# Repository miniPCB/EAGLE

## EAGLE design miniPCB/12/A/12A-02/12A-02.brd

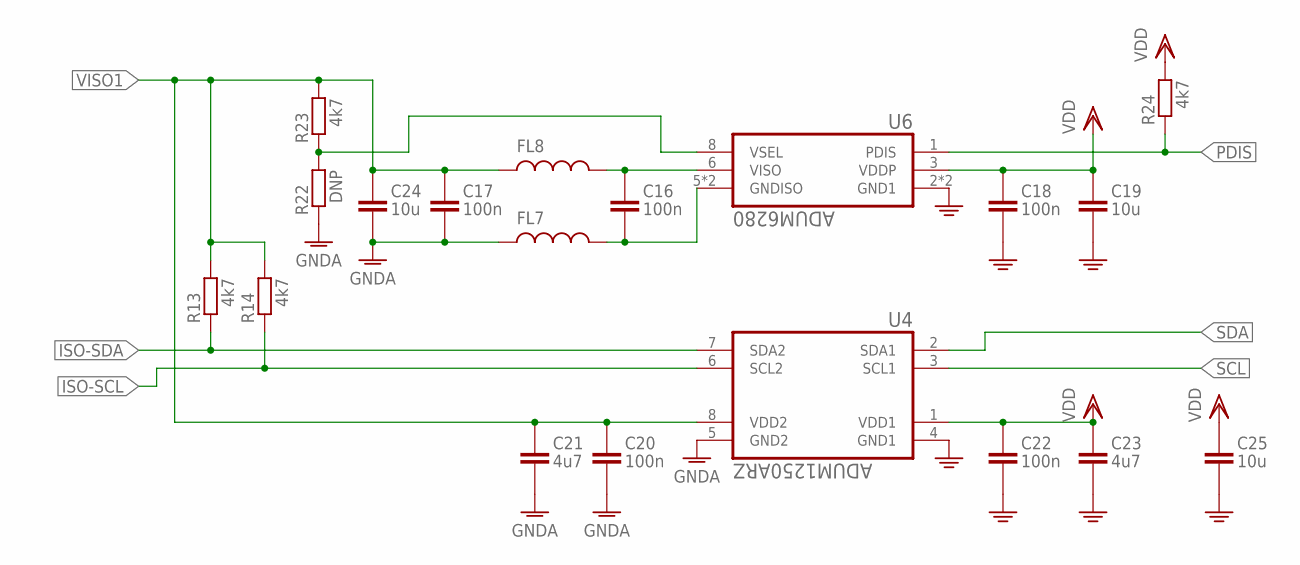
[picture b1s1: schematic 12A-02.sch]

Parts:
C16, C17, C18, C20, C22: 100n; C0402
C19, C24, C25: 10u; C0805
C21, C23: 4u7; C0402
FL7, FL8: BLM03HG601SZ1D; R0402
R13, R14, R23, R24: 4k7; R0402
R22: DNP; R0402
U4: ADUM1250ARZ; SOIC127P600X175-8N
U6: ADUM6280; SOIC127P600X175-8N

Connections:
GND: C18.2 (-), C19.2ASDF (-), C22.2 (-), C23.2 (-), C25.2ASDF (-), U4.4 (GND1), U6.2 (GND1), U6.4 (GND1)
GNDA: C17.2 (-), C20.2 (-), C21.2 (-), C24.2ASDF (-), FL7.1, R22.1, U4.5 (GND2)
ISO-SCL: R14.1, U4.6 (SCL2)
ISO-SDA: R13.1, U4.7 (SDA2)
unnamed: R22.2, R23.1, U6.8 (VSEL)
unnamed: C16.2 (-), FL7.2, U6.5 (GNDISO), U6.7 (GNDISO)
unnamed: C16.1 (+), FL8.2, U6.6 (VISO)
PDIS: R24.1, U6.1 (PDIS)
SCL: U4.3 (SCL1)
SDA: U4.2 (SDA1)
VDD: C18.1 (+), C19.1ASD (+), C22.1 (+), C23.1 (+), C25.1ASD (+), R24.2, U4.1 (VDD1), U6.3 (VDDP)
VISO1: C17.1 (+), C20.1 (+), C21.1 (+), C24.1ASD (+), FL8.1, R13.2, R14.2, R23.2, U4.8 (VDD2)

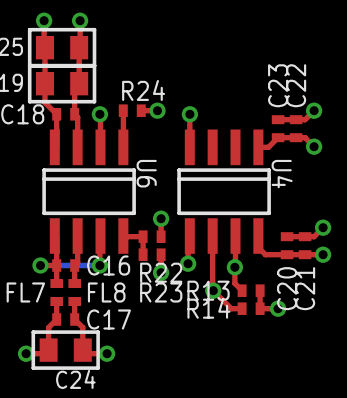
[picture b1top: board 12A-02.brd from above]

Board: 2 copper layers, 19 parts (0 on the bottom side), 10 nets.

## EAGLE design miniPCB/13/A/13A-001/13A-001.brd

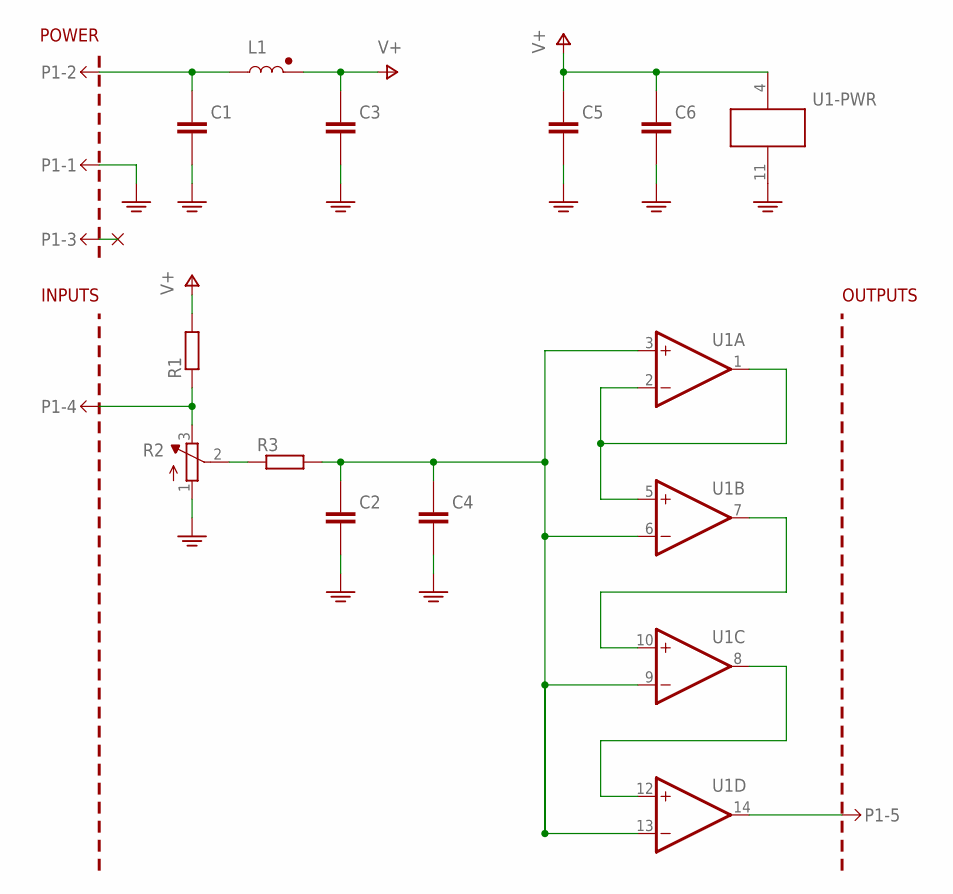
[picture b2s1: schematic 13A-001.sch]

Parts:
C1, C3: CAPACITOR_10; C5MM
C2, C4, C5, C6: CAPACITORTHD; C050-024X044
L1: INDUCTORRFS1113; L/RFS1113
P1-: MINIPCB_5P50X50; MINIPCB_5P_50X50MM
R1, R3: RESISTORTHD; 0204/10
R2: TRIMPOT0.100THD; TRIM_0100
U1: OPAMP_QUADTHD; DIL14

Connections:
GND: C1.-, C2.2 (-), C3.-, C4.2 (-), C5.2 (-), C6.2 (-), P1-.1, R2.1 (A), U1.11 (V-)
unnamed: P1-.4, R1.1, R2.3 (E)
unnamed: R2.2 (S), R3.1
unnamed: C2.1 (+), C4.1 (+), R3.2, U1.3 (+IN), U1.6 (-IN), U1.9 (-IN), U1.13 (-IN)
unnamed: U1.1 (OUT), U1.2 (-IN), U1.5 (+IN)
unnamed: C1.+, L1.2, P1-.2
unnamed: U1.7 (OUT), U1.10 (+IN)
unnamed: U1.8 (OUT), U1.12 (+IN)
unnamed: P1-.5, U1.14 (OUT)
V+: C3.+, C5.1 (+), C6.1 (+), L1.1, R1.2, U1.4 (V+)

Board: 2 copper layers, 12 parts (0 on the bottom side), 10 nets, no tracks yet.

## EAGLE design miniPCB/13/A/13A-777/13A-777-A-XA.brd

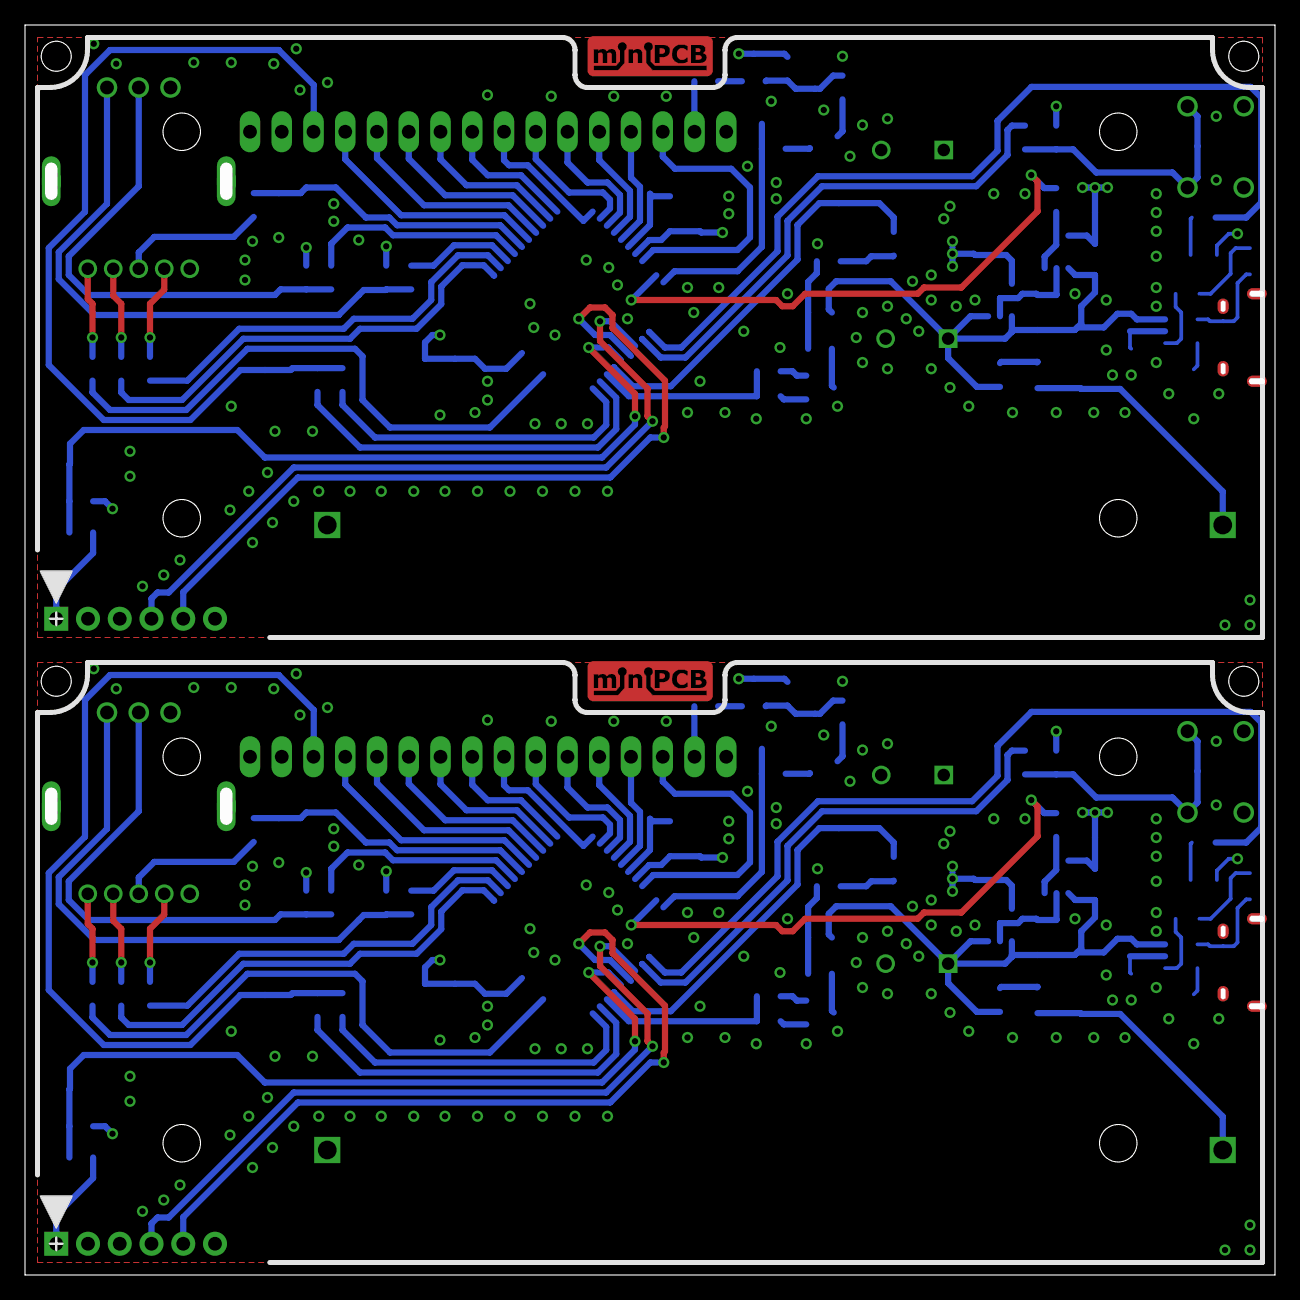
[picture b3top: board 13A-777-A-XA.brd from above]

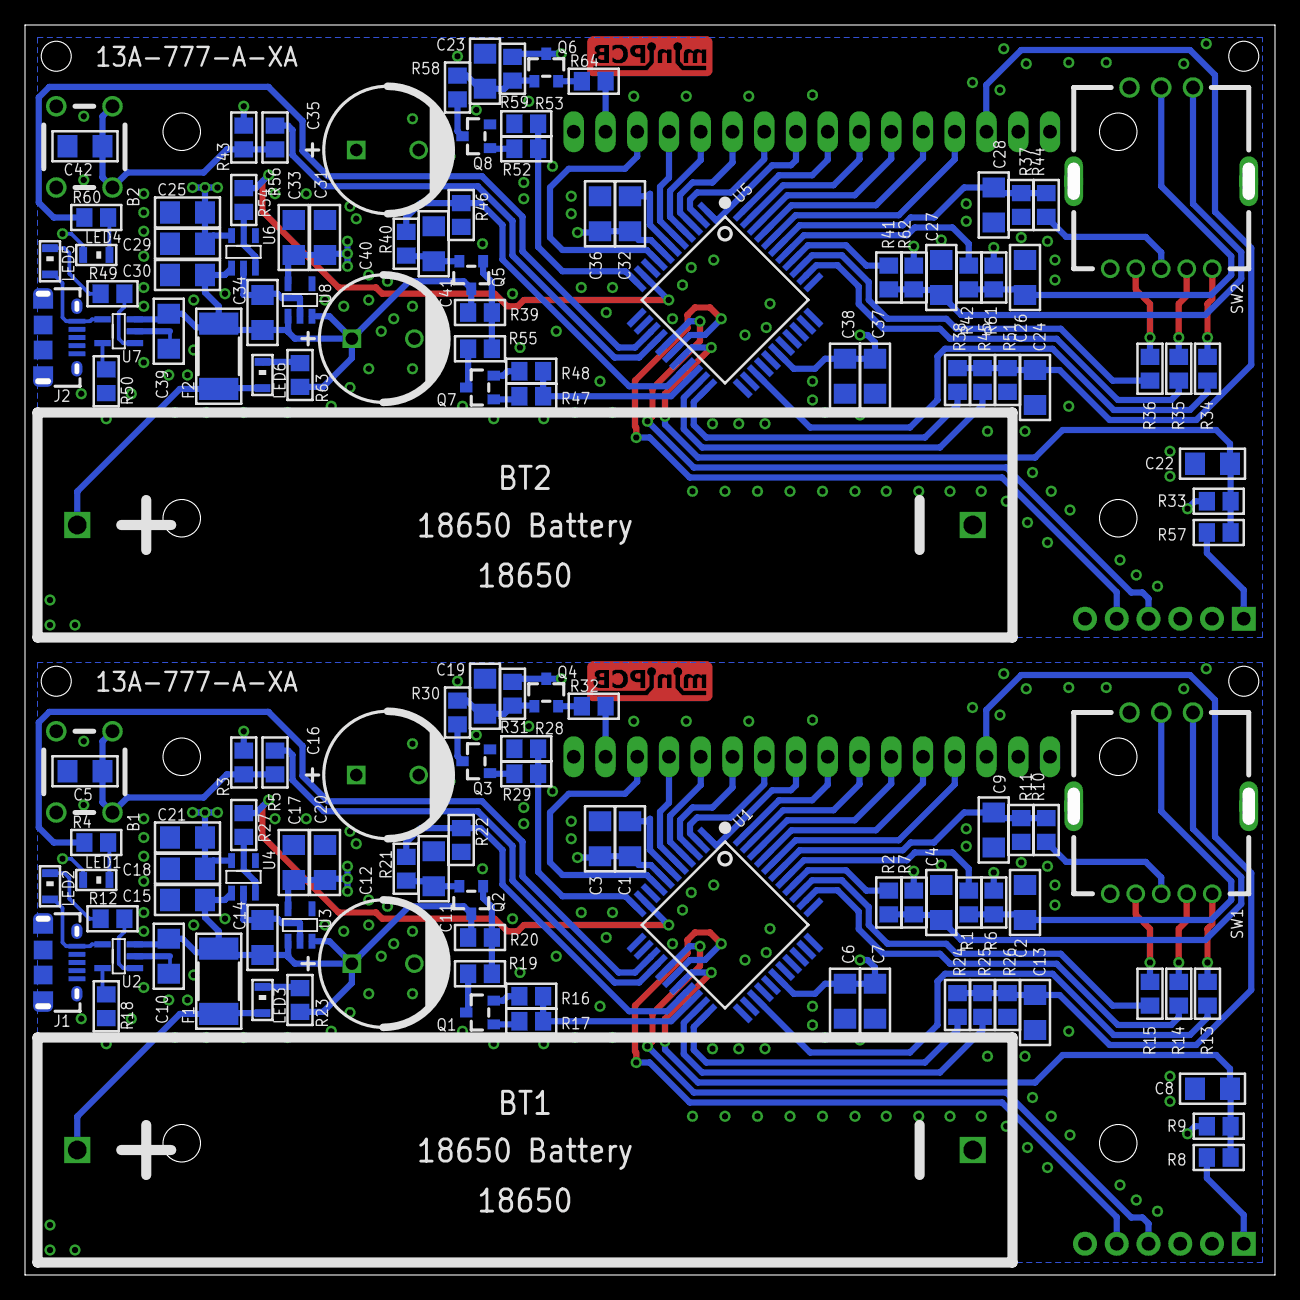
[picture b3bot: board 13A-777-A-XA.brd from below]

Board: 4 copper layers, 100.0 x 100.0 mm, 145 parts (138 on the bottom side), 116 nets.

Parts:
B1, B2: 6X6MM
BT1, BT2: 18650; BATTERY-18650-1-NOHOLES
C1, C2, C4, C5, C6, C8, C9, C11, C13, C14, C15, C19, C20, C21, C22, C23, C24, C25, C26, C27, C28, C30, C31, C32, C34, C38, C41, C42: 680n; C1206
C3, C7, C17, C18, C29, C33, C36, C37: 6n8; C1206
C10, C39: 4u7; C1206
C12, C16, C35, C40: 22u 25V; C5MM
E$1: MINIPCB_PANEL_IMAGEFRAME
F1, F2: 1A; 1812L010DR
J1, J2: USB_MICRO
LED1, LED2, LED3, LED4, LED5, LED6: CHIP-LED0805
PCB, PCB1: PCB-50/100-0; MINIPCB_0P_50X100MM
Q1, Q3, Q7, Q8: 2N7002; SOT23
Q2, Q4, Q5, Q6: NTR2101P; SOT23
R1, R2, R6, R7, R9, R16, R17, R19, R28, R29, R30, R33, R41, R42, R47, R48, R52, R53, R55, R58, R61, R62: 10k; R0805
R3, R5, R10, R43, R44, R56: 10K; R0805
R4, R8, R12, R13, R14, R15, R23, R27, R32, R34, R35, R36, R49, R54, R57, R60, R63, R64: 150; R0805
R11, R20, R31, R37, R39, R59: 499K; R0805
R18, R50: 2K; R0805
R21, R22, R40, R46: 4K99; R0805
R24, R25, R26, R38, R45, R51: 1K; R0805
SW1, SW2: PEL12T; SWITCH-ROTARY_ENCODER-12MM
U1, U5: PIC16F1789T-I/PT; SQFP-S-10X10-44
U2, U7: MCP73831; SOT-23-5_MC_MCH
U3, U4, U6, U8: ADP150AUJZ-3.3-R7; SOT25
U$1, U$2: PICKIT3ARROW; PINS_6_PICKIT3
X1, X2: HD44780LCD-1602; LCD1602

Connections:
+3V1: C31.+, C32.+, C33.+, C36.+, C37.+, C38.+, LED4.A, R33.2, R43.2, U5.7, U5.28, U8.5, U$2.2
+3V3: C1.+, C3.+, C6.+, C7.+, C17.+, C20.+, LED1.A, R3.2, R9.2, U1.7, U1.28, U3.5, U$1.2
+3V3-LCD: C16.+, C18.+, C21.+, Q4.3, R6.2, R7.2, R31.1, SW1.5, U4.5, X1.2
+3V3-LCD1: C25.+, C29.+, C35.+, Q6.3, R59.1, R61.2, R62.2, SW2.5, U6.5, X2.2
B1: B1.3.B, B1.4.B, C5.+, R3.1, R5.2
B2: B2.3.B, B2.4.B, C42.+, R43.1, R56.2
BT+: BT1.+, F1.1, LED3.A
BT+1: BT2.+, F2.1, LED6.A
BUTTON: R5.1, U1.15
BUTTON1: R56.1, U5.15
ENC_A: R1.2, U1.38
ENC_A1: R42.2, U5.38
ENC_B: R2.2, U1.37
ENC_B1: R41.2, U5.37
ENC_BLUE: R15.1, U1.36
ENC_BLUE1: R36.1, U5.36
ENC_GREEN: R14.1, U1.35
ENC_GREEN1: R35.1, U5.35
ENC_RED: R13.1, U1.25
ENC_RED1: R34.1, U5.25
ENC_SW: C9.+, R10.1, R11.2, U1.39
ENC_SW1: C28.+, R37.2, R44.1, U5.39
GND: B1.1.A, B1.2.A, BT1.1, C1.-, C2.-, C3.-, C4.-, C5.-, C6.-, C7.-, C8.-, C9.-, C10.-, C11.-, C12.-, C13.-, C14.-, C15.-, C16.-, C17.-, C18.-, C19.-, C20.-, C21.-, J1.5, Q1.2, Q3.2, R11.1, R16.2, R18.2, R22.1, R26.2, R28.2, SW1.C, U1.6, U1.29, U2.2, U3.2, U4.2, U$1.3, X1.1, X1.16
GND1: B2.1.A, B2.2.A, BT2.1, C22.-, C23.-, C24.-, C25.-, C26.-, C27.-, C28.-, C29.-, C30.-, C31.-, C32.-, C33.-, C34.-, C35.-, C36.-, C37.-, C38.-, C39.-, C40.-, C41.-, C42.-, J2.5, Q7.2, Q8.2, R37.1, R46.1, R48.2, R50.2, R51.2, R53.2, SW2.C, U5.6, U5.29, U6.2, U7.2, U8.2, U$2.3, X2.1, X2.16
ICSPCLK: U1.17, U$1.5
ICSPCLK1: U5.17, U$2.5
ICSPDAT: U1.16, U$1.4
ICSPDAT1: U5.16, U$2.4
LCD-BACKLIGHT-A: R32.2, X1.15
LCD-BACKLIGHT-A1: R64.2, X2.15
LCD-BACKLIGHT-ENABLE: R28.1, R29.2, U1.11
LCD-BACKLIGHT-ENABLE1: R52.2, R53.1, U5.11
LCD-D0: U1.43, X1.7
LCD-D1: U1.44, X1.8
LCD-D2: U1.1, X1.9
LCD-D3: U1.2, X1.10
LCD-D4: U1.3, X1.11
LCD-D5: U1.4, X1.12
LCD-D6: U1.5, X1.13
LCD-D7: U1.8, X1.14
LCD-D8: U5.44, X2.8
LCD-D9: U5.1, X2.9
LCD-D10: U5.2, X2.10
LCD-D11: U5.43, X2.7
LCD-D12: U5.3, X2.11
LCD-D13: U5.4, X2.12
LCD-D14: U5.5, X2.13
LCD-D15: U5.8, X2.14
LCD-RE: U1.42, X1.6
LCD-RE1: U5.42, X2.6
LCD-RS: U1.40, X1.4
LCD-RS1: U5.40, X2.4
LCD-RW: U1.41, X1.5
LCD-RW1: U5.41, X2.5
LCD-V0: C13.+, R24.1, R25.1, R26.1, X1.3
LCD-V1: C24.+, R38.1, R45.1, R51.1, X2.3
LCD_ENABLE: R27.2, U1.10
LCD_ENABLE1: R54.2, U5.10
LED1: R4.1, U1.14
LED1.K: LED1.C, R4.2
LED1.K1: LED4.C, R60.2
LED2: R60.1, U5.14
LED2.K: LED2.C, R12.2
LED2.K1: LED5.C, R49.2
LED3K: LED3.C, R23.2
LED3K1: LED6.C, R63.2
MCLR: C8.+, R8.1, R9.1, U1.18
MCLR1: C22.+, R33.1, R57.1, U5.18
P1-1: R8.2, U$1.1
P1-2: R57.2, U$2.1
PROG: R18.1, U2.5
PROG1: R50.1, U7.5
Q1.D: Q1.3, R19.2
Q1.D1: Q7.3, R55.2
Q1.G: Q1.1, R17.1
Q1.G1: Q7.1, R47.1
Q2.G: Q2.1, R19.1, R20.2
Q2.G1: Q5.1, R39.2, R55.1
Q2.S: C11.+, Q2.2, R21.2
Q2.S1: C41.+, Q5.2, R40.2
Q3.D: Q3.3, R30.2
Q3.D1: Q8.3, R58.2
Q3.G: Q3.1, R29.1
Q3.G1: Q8.1, R52.1
Q4.G: C19.+, Q4.1, R30.1, R31.2
Q4.G1: C23.+, Q6.1, R58.1, R59.2
Q4.S: Q4.2, R32.1
Q4.S1: Q6.2, R64.1
RA0: R21.1, R22.2, U1.19
RA1: R16.1, R17.2, U1.20
RA2: R25.2, U1.21
RA3: R24.2, U1.22
RA4: R45.2, U5.21
RA5: R40.1, R46.2, U5.19
RA6: R38.2, U5.22
RA7: R47.2, R48.1, U5.20
SW1.1: R13.2, SW1.1
SW1.2: R14.2, SW1.2
SW1.3: R10.2, SW1.3
SW1.4: R15.2, SW1.4
SW1.5: R34.2, SW2.1
SW1.6: R35.2, SW2.2
SW1.7: R36.2, SW2.4
SW1.8: R44.2, SW2.3
SW1.A: C2.+, R1.1, R6.1, SW1.B
SW1.A1: C26.+, R42.1, R61.1, SW2.B
SW1.B: C4.+, R2.1, R7.1, SW1.A
SW1.B1: C27.+, R41.1, R62.1, SW2.A
U4.1: R12.1, U2.1
U4.2: R49.1, U7.1
U4.3: R27.1, U4.3
U4.4: R54.1, U6.3
VBAT: C10.+, C12.+, C14.+, C15.+, F1.2, Q2.3, R20.1, R23.1, U2.3, U3.1, U3.3, U4.1
VBAT1: C30.+, C34.+, C39.+, C40.+, F2.2, Q5.3, R39.1, R63.1, U6.1, U7.3, U8.1, U8.3
VUSB: J1.1, LED2.A, U2.4
VUSB1: J2.1, LED5.A, U7.4

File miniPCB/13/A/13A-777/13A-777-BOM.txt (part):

Partlist exported from C:/Repos/miniPCB/EAGLE/miniPCB/13/A/13A-777/13A-777.sch at 2/3/2023 6:44 PM

Qty Value             Device                               Package                    Parts                                                         Description                                                   ARROW_PART_NUMBER ARROW_PRICE-STOCK                                                    COPYRIGHT                                                DESCRIPTION                                                   HEIGHT MANUFACTURER_NAME MANUFACTURER_PART_NUMBER MFR_NAME  MOUSER_PART_NUMBER MOUSER_PRICE-STOCK                                                                              MOUSER_TESTING_PART_NUMBER MOUSER_TESTING_PRICE-STOCK PART_NUMBER  REVISION
3                     LEDCHIP-LED0805                      CHIP-LED0805               LED1, LED2, LED3                                              LED                                                                                                                                                                                                                                                                                                                                                                                                                                                                                                                                   
1                     PUSHBUTTON6X6MM                      6X6MM                      B1                                                            Tactile push button switch                                                                                                                                                                                                                                                                                                                                                                                                                                                                                                            
1                     USB                                  USB_MICRO                  J1                                                                                                                                                                                                                                                                                                                                                                                                                                                                                                                                                                                                  
3   10K               RESISTORSMD                          R0805                      R3, R5, R10                                                                                                                                                                                                                                                                                                                                                                                                                                                                                                                                                                                         
11  10k               RESISTORSMD                          R0805                      R1, R2, R6, R7, R9, R16, R17, R19, R28, R29, R30                                                                                                                                                                                                                                                                                                                                                                                                                                                                                                                                                    
9   150               RESISTORSMD                          R0805                      R4, R8, R12, R13, R14, R15, R23, R27, R32                                                                                                                                                                                                                                                                                                                                                                                                                                                                                                                                                           
1   18650             BATTERY18650-NOHOLES                 BATTERY-18650-1-NOHOLES    BT1                                                           2xAAA battery holder for VIVA                                                                                                                                                                                                                                                                                                                                                                                                                                                                                                         
1   1A                FUSE-1812-1A                         1812L010DR                 F1                                                            Resettable Fuses - PPTC PTC 60V POLYFUSE SURF MOUNT 1812 0.5A 1812L050/60MR     https://www.arrow.com/en/products/1812l05060mr/littelfuse?re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                                                          Resettable Fuses - PPTC PTC 60V POLYFUSE SURF MOUNT 1812 0.5A 1.25mm LITTELFUSE        1812L050/60MR                      576-1812L050/60MR  https://www.mouser.co.uk/ProductDetail/Littelfuse/1812L050-6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                                                                            
3   1K                RESISTORSMD                          R0805                      R24, R25, R26                                                                                                                                                                                                                                                                                                                                                                                                                                                                                                                                                                                       
2   22u 25V           CAPACITOR_10                         C5MM                       C12, C16                                                                                                                                                                                                                                                                                                                                                                                                                                                                                                                                                                                            
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
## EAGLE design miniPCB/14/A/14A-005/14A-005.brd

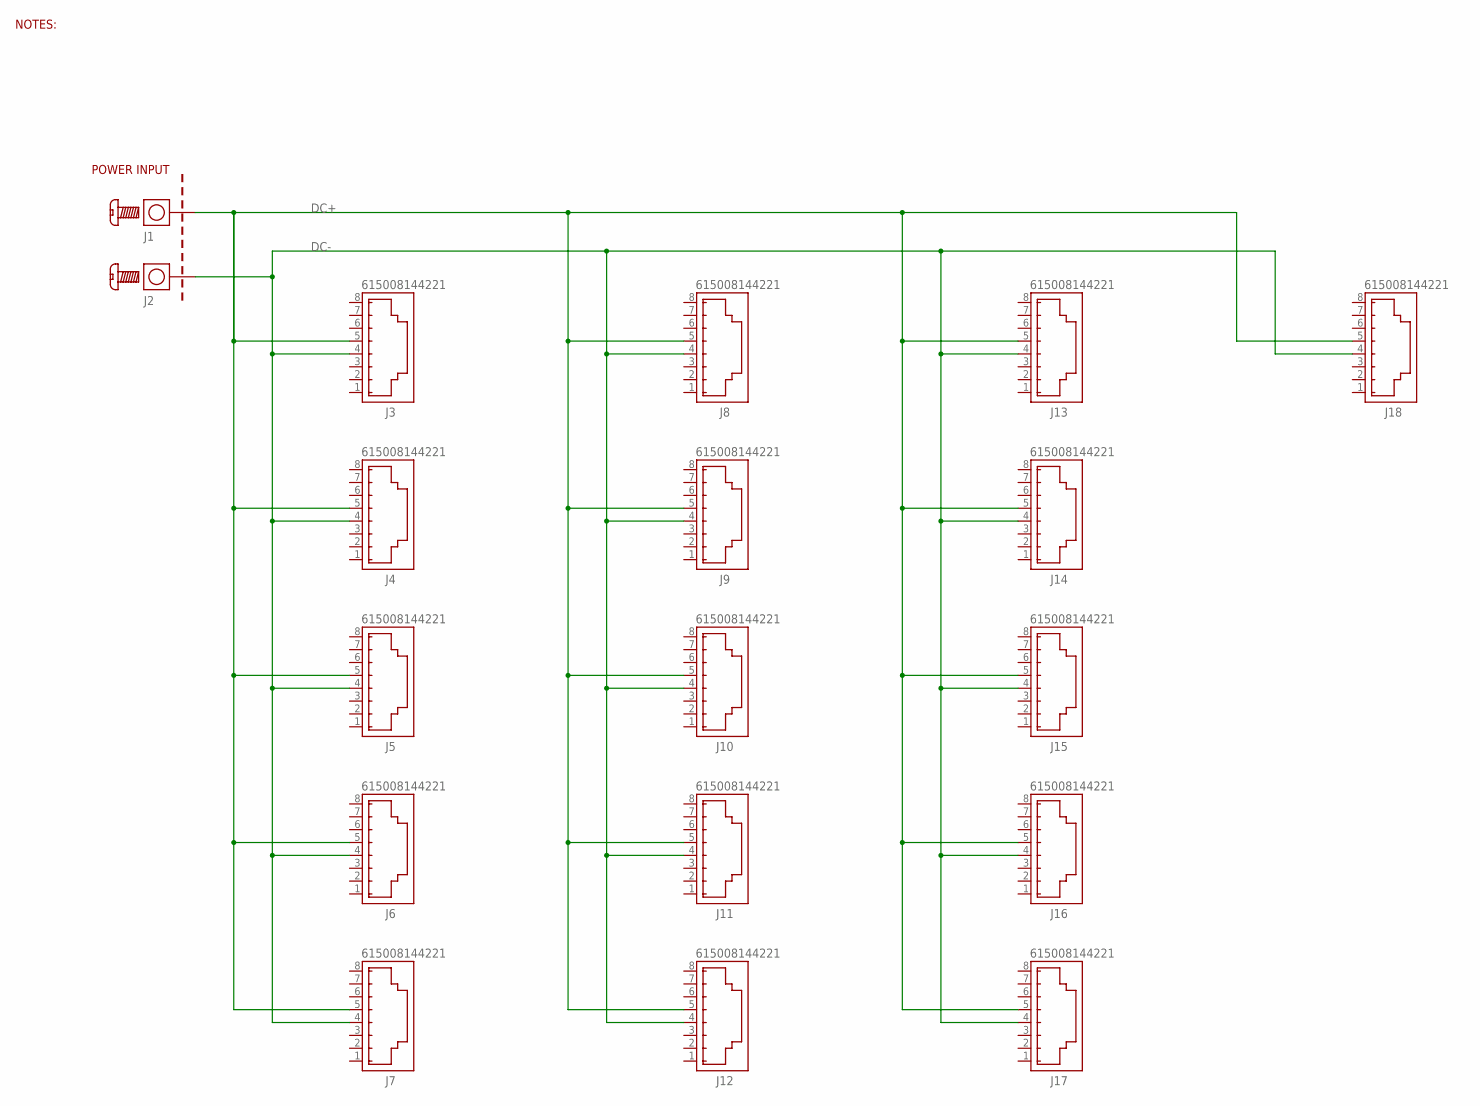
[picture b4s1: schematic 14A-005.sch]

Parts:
-: POWER INPUT; MINIPCB_DOCK_100X100; PART_NUMBER 14A-005
J1, J2: SCREW-TERMINAL; SCREW-TERMINAL-M3
J3, J4, J5, J6, J7, J8, J9, J10, J11, J12, J13, J14, J15, J16, J17, J18: 615008144221

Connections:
DC+: J1.1, J1.2, J1.3, J1.4, J3.5 (4), J4.5 (4), J5.5 (4), J6.5 (4), J7.5 (4), J8.5 (4), J9.5 (4), J10.5 (4), J11.5 (4), J12.5 (4), J13.5 (4), J14.5 (4), J15.5 (4), J16.5 (4), J17.5 (4), J18.5 (4)
DC-: J2.1, J2.2, J2.3, J2.4, J3.4 (5), J4.4 (5), J5.4 (5), J6.4 (5), J7.4 (5), J8.4 (5), J9.4 (5), J10.4 (5), J11.4 (5), J12.4 (5), J13.4 (5), J14.4 (5), J15.4 (5), J16.4 (5), J17.4 (5), J18.4 (5)

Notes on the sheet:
NOTES:

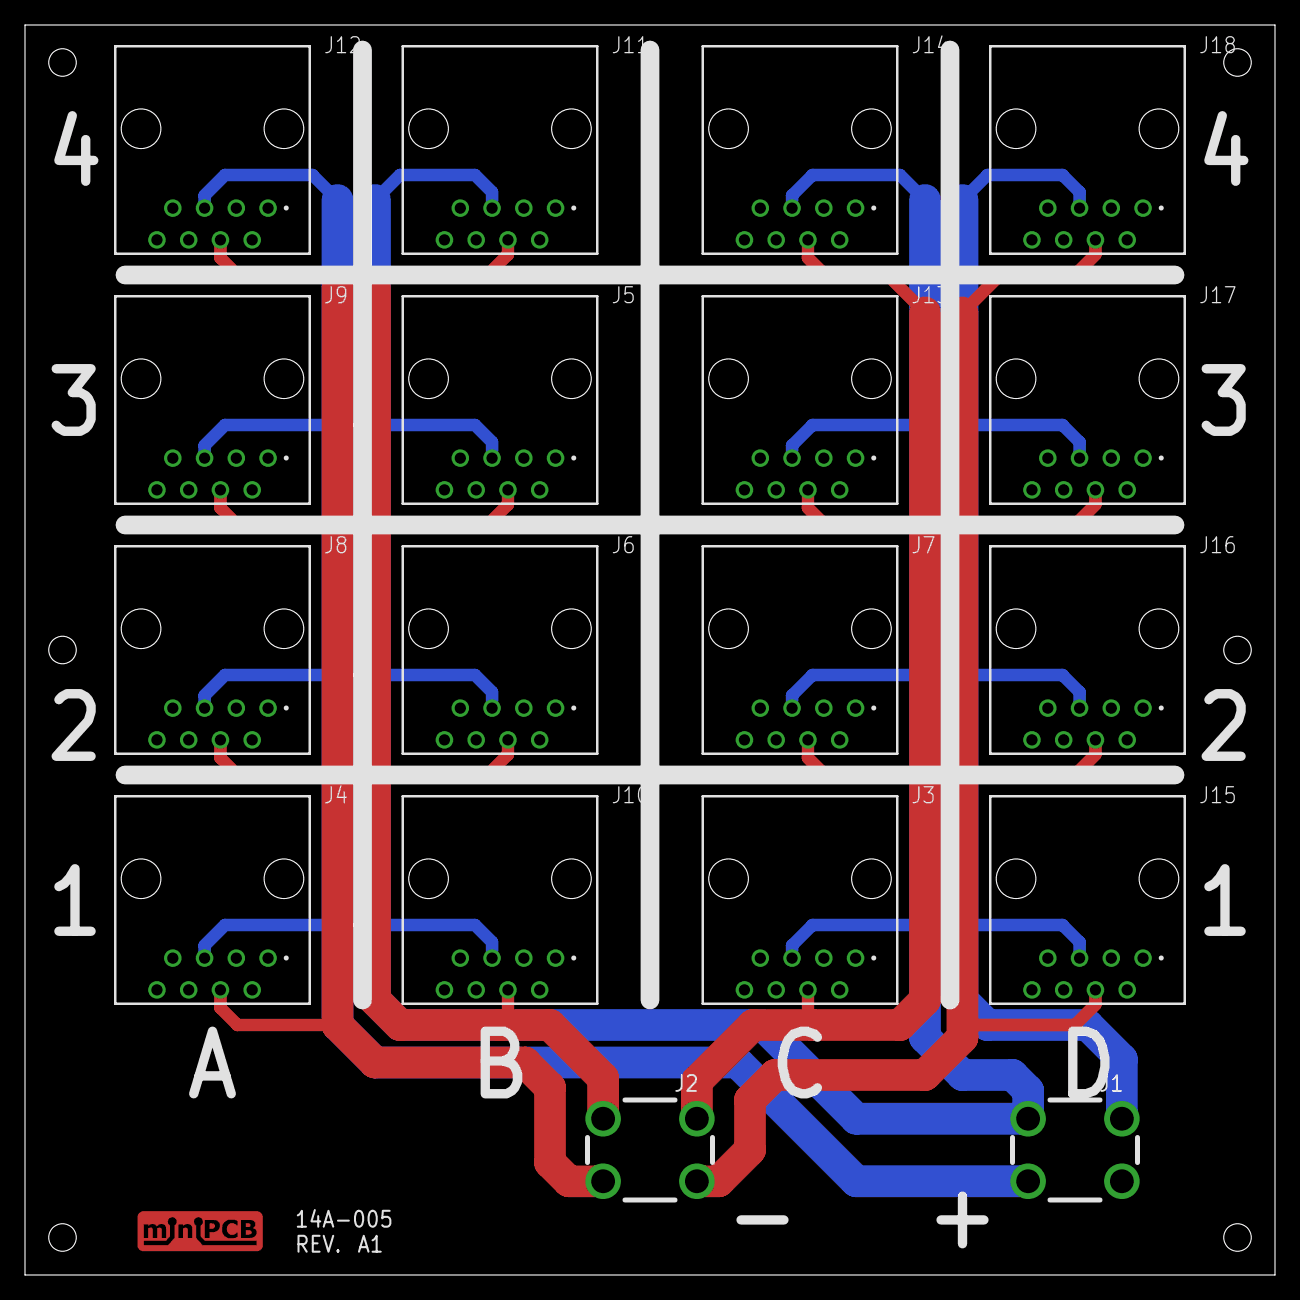
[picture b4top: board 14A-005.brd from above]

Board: 2 copper layers, 100.0 x 100.0 mm, 19 parts (0 on the bottom side), 2 nets.

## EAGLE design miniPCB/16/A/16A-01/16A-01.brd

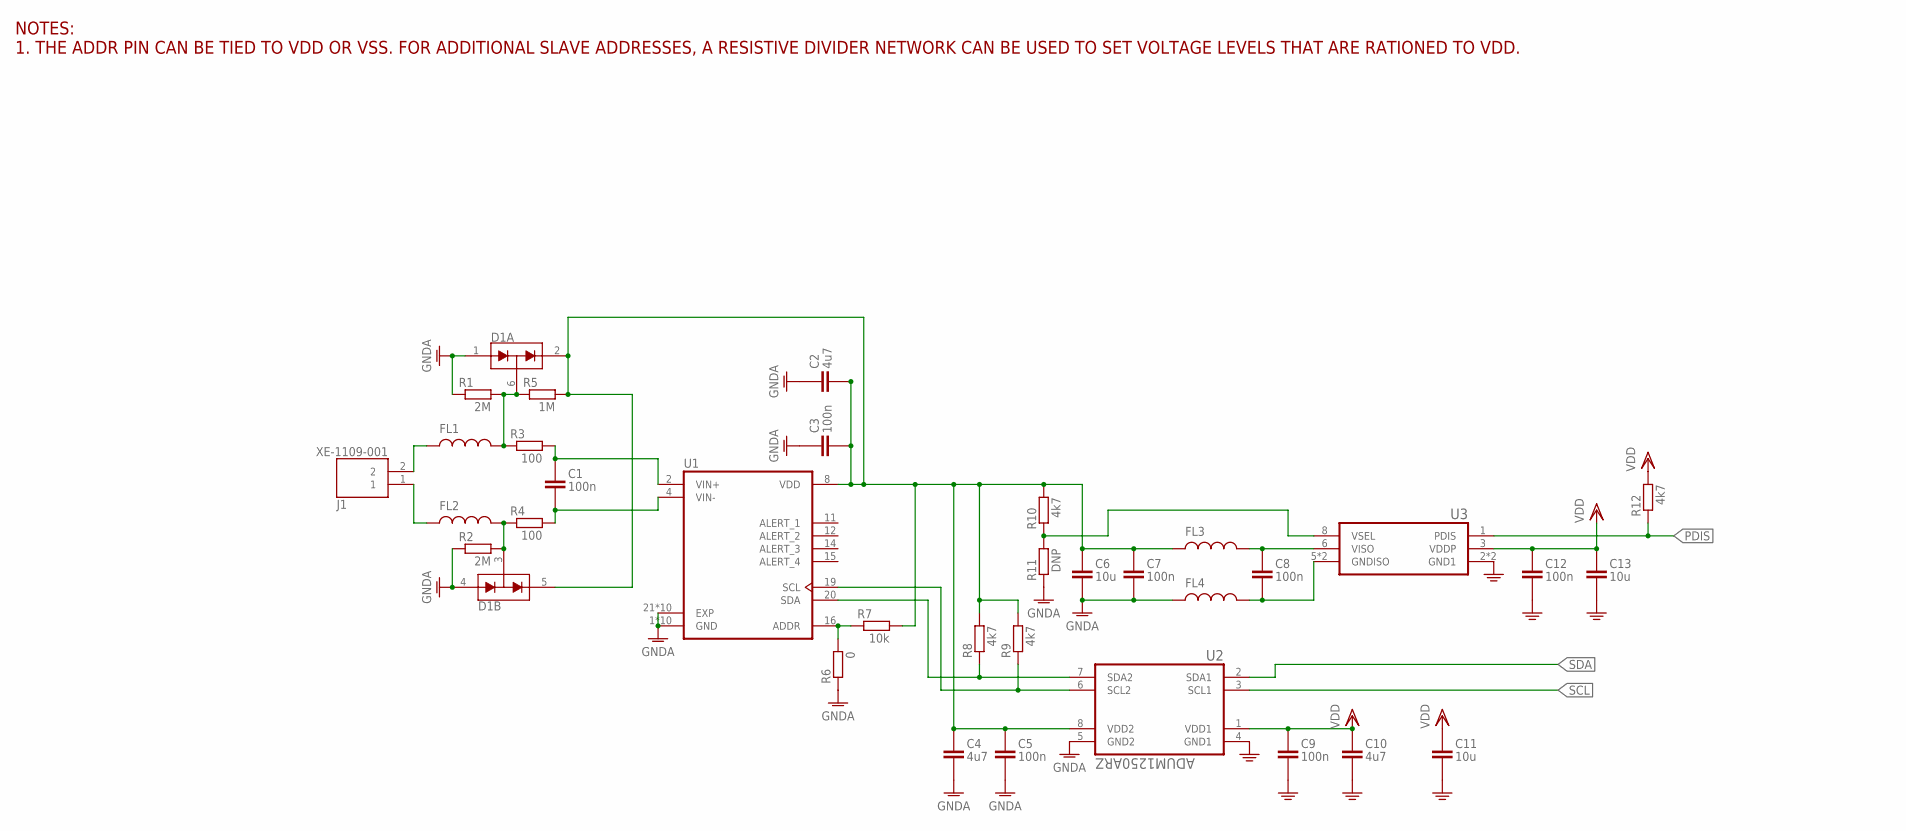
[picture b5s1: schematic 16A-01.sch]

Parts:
C1, C3, C5, C7, C8, C9, C12: 100n; C0402
C2, C4, C10: 4u7; C0402
C6, C11, C13: 10u; C0805
D1: SDA004-7; SOT363
FL1, FL2, FL3, FL4: BLM03HG601SZ1D; R0402
J1: XE-1109-001
R1, R2: 2M; R0402
R3, R4: 100; R0402
R5: 1M; R0402
R6: 0; R0402
R7: 10k; R0402
R8, R9, R10, R12: 4k7; R0402
R11: DNP; R0402
U1: MCP9600T-I/MX; QFN65P500X500X100-21N_MCP9600T-I/MX
U2: ADUM1250ARZ; SOIC127P600X175-8N
U3: ADUM6280; SOIC127P600X175-8N

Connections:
GND: C9.2 (-), C10.2 (-), C11.2ASDF (-), C12.2 (-), C13.2ASDF (-), U2.4 (GND1), U3.2 (GND1), U3.4 (GND1)
GNDA: C2.1 (+), C3.1 (+), C4.2 (-), C5.2 (-), C6.2ASDF (-), C7.2 (-), D1.1 (A1), D1.4 (A1), FL4.1, R1.1, R2.1, R6.1, R11.1, U1.1 (GND), U1.3 (GND), U1.5 (GND), U1.6 (GND), U1.7 (GND), U1.9 (GND), U1.10 (GND), U1.13 (GND), U1.17 (GND), U1.18 (GND), U1.21 (EXP), U1.22 (EXP), U1.23 (EXP), U1.24 (EXP), U1.25 (EXP), U1.26 (EXP), U1.27 (EXP), U1.28 (EXP), U1.29 (EXP), U1.30 (EXP), U2.5 (GND2)
unnamed: D1.6 (COM), FL1.2, R1.2, R3.1, R5.1
unnamed: R9.1, U1.19 (SCL), U2.6 (SCL2)
unnamed: R8.1, U1.20 (SDA), U2.7 (SDA2)
unnamed: C8.2 (-), FL4.2, U3.5 (GNDISO), U3.7 (GNDISO)
unnamed: C8.1 (+), FL3.2, U3.6 (VISO)
unnamed: R10.1, R11.2, U3.8 (VSEL)
unnamed: R6.2, R7.1, U1.16 (ADDR)
unnamed: C1.1 (+), R3.2, U1.2 (VIN+)
unnamed: D1.3 (COM), FL2.2, R2.2, R4.1
unnamed: C1.2 (-), R4.2, U1.4 (VIN-)
unnamed: FL1.1, J1.2
unnamed: FL2.1, J1.1
PDIS: R12.1, U3.1 (PDIS)
SCL: U2.3 (SCL1)
SDA: U2.2 (SDA1)
VDD: C9.1 (+), C10.1 (+), C11.1ASD (+), C12.1 (+), C13.1ASD (+), R12.2, U2.1 (VDD1), U3.3 (VDDP)
VISO: C2.2 (-), C3.2 (-), C4.1 (+), C5.1 (+), C6.1ASD (+), C7.1 (+), D1.2 (C2), D1.5 (C2), FL3.1, R5.2, R7.2, R8.2, R9.2, R10.2, U1.8 (VDD), U2.8 (VDD2)

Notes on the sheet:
NOTES: 1. THE ADDR PIN CAN BE TIED TO VDD OR VSS. FOR ADDITIONAL SLAVE ADDRESSES, A RESISTIVE DIVIDER NETWORK CAN BE USED TO SET VOLTAGE LEVELS THAT ARE RATIONED TO VDD.

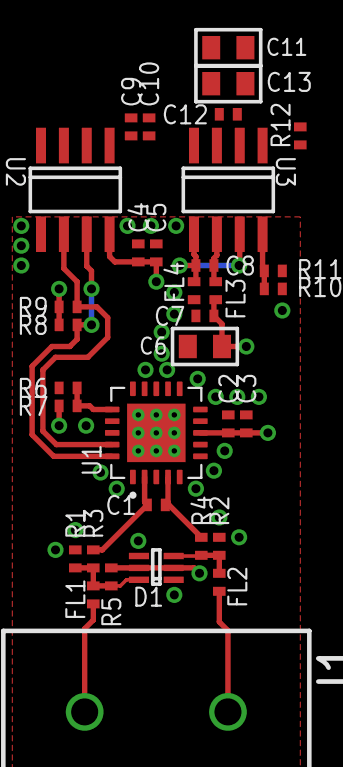
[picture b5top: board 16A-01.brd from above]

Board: 4 copper layers, 34 parts (0 on the bottom side), 17 nets.

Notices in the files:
parts and their libraries:
COPYRIGHT: Copyright (C) 2023 Ultra Librarian. All rights reserved.
